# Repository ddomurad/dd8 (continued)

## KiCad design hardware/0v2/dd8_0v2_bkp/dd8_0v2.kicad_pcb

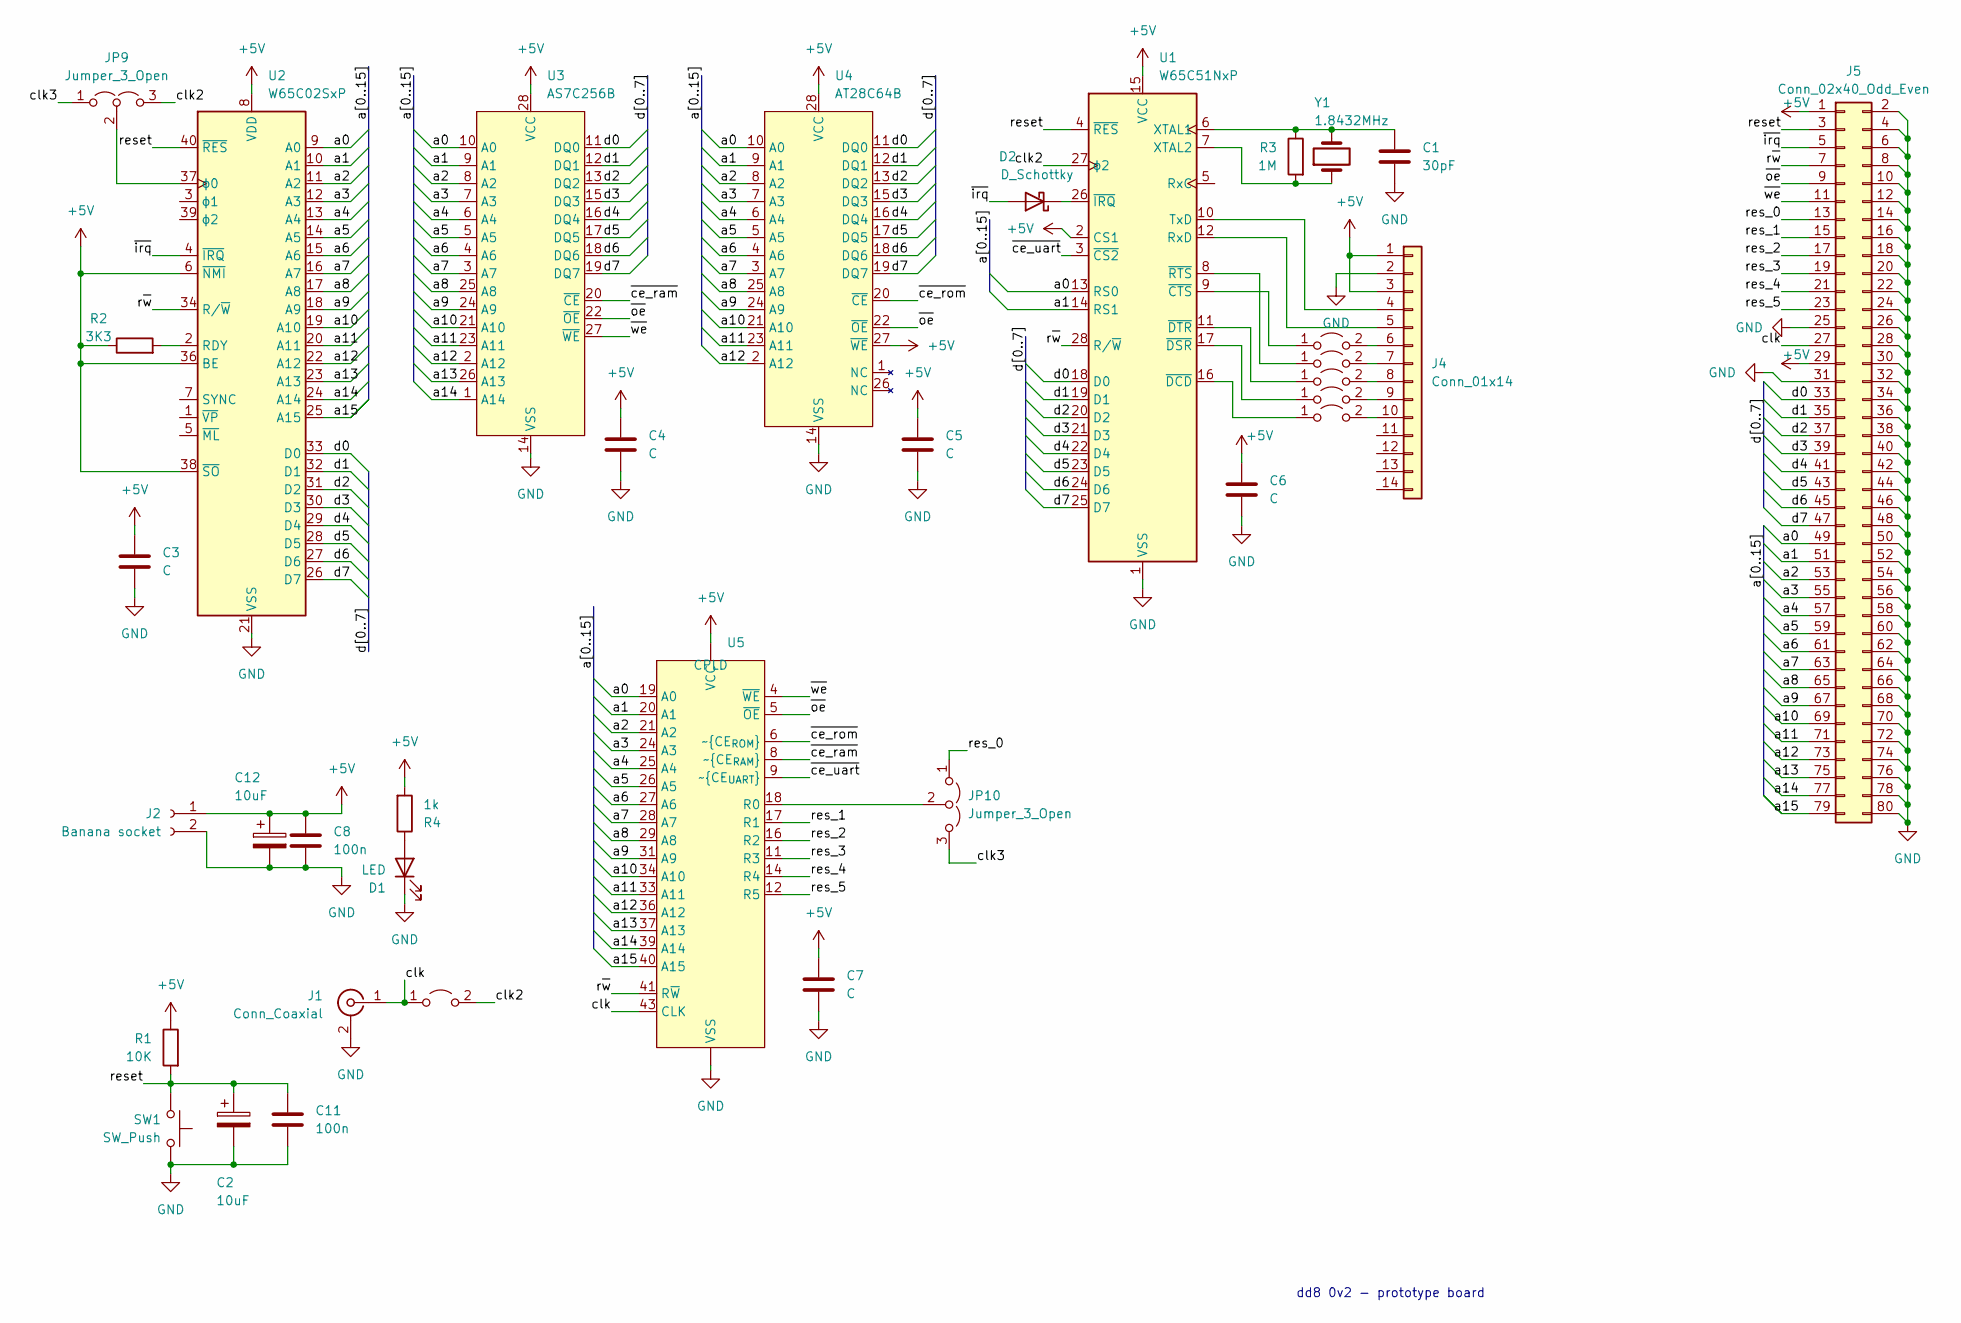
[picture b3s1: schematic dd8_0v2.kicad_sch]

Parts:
C1: 30pF; C_Disc_D3.0mm_W1.6mm_P2.50mm
C2, C12: 10uF; CP_Radial_D5.0mm_P2.50mm
C3, C4, C5, C6, C7: C; C_Disc_D3.0mm_W1.6mm_P2.50mm
C8, C11: 100n; C_Disc_D3.0mm_W1.6mm_P2.50mm
D1: LED; LED_D3.0mm
D2: D_Schottky; D_A-405_P7.62mm_Horizontal
J1: Conn_Coaxial; BNC_Amphenol_B6252HB-NPP3G-50_Horizontal
J2: Banana socket; Bannana_Jack_2Pin
J4: Conn_01x14; PinHeader_2x07_P2.54mm_Vertical
J5: Conn_02x40_Odd_Even; PinSocket_2x40_P2.54mm_Vertical
JP1, JP2, JP3, JP4, JP5, JP6: Jumper_2_Open; SolderJumper-2_P1.3mm_Open_Pad1.0x1.5mm
JP9, JP10: Jumper_3_Open; SolderJumper-3_P1.3mm_Open_Pad1.0x1.5mm
R1: 10K; R_Axial_DIN0204_L3.6mm_D1.6mm_P2.54mm_Vertical
R2: 3K3; R_Axial_DIN0204_L3.6mm_D1.6mm_P2.54mm_Vertical
R3: 1M; R_Axial_DIN0204_L3.6mm_D1.6mm_P5.08mm_Horizontal
R4: 1k; R_Axial_DIN0204_L3.6mm_D1.6mm_P2.54mm_Vertical
SW1: SW_Push; SW_PUSH_6mm_H5mm
U1: W65C51NxP; DIP-28_W15.24mm
U2: W65C02SxP; DIP-40_W15.24mm
U3: AS7C256B; DIP-28_W7.62mm
U4: AT28C64B; DIP_Socket-28_W6.9_W7.62_W10.16_W12.7_W13.5_3M_228-4817-00-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
U5: CPLD; PLCC-44_THT-Socket
Y1: 1.8432MHz; Crystal_HC18-U_Vertical

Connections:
+5V: C3.1, C4.1, C5.1, C6.1, C7.1, C8.1, C12.1, J2.1, J4.1, J4.3, J5.1, J5.29, R1.1, R2.1, R4.2, U1.2 (CS1), U1.15 (VCC), U2.6 (~NMI), U2.8 (VDD), U2.36 (BE), U2.38 (~SO), U3.28 (VCC), U4.27 (~WE), U4.28 (VCC), U5. (VCC)
/a0: J5.49, U1.13 (RS0), U2.9 (A0), U3.10 (A0), U4.10 (A0), U5.19 (A0)
/a1: J5.51, U1.14 (RS1), U2.10 (A1), U3.9 (A1), U4.9 (A1), U5.20 (A1)
/a2: J5.53, U2.11 (A2), U3.8 (A2), U4.8 (A2), U5.21 (A2)
/a3: J5.55, U2.12 (A3), U3.7 (A3), U4.7 (A3), U5.24 (A3)
/a4: J5.57, U2.13 (A4), U3.6 (A4), U4.6 (A4), U5.25 (A4)
/a5: J5.59, U2.14 (A5), U3.5 (A5), U4.5 (A5), U5.26 (A5)
/a6: J5.61, U2.15 (A6), U3.4 (A6), U4.4 (A6), U5.27 (A6)
/a7: J5.63, U2.16 (A7), U3.3 (A7), U4.3 (A7), U5.28 (A7)
/a8: J5.65, U2.17 (A8), U3.25 (A8), U4.25 (A8), U5.29 (A8)
/a9: J5.67, U2.18 (A9), U3.24 (A9), U4.24 (A9), U5.31 (A9)
/a10: J5.69, U2.19 (A10), U3.21 (A10), U4.21 (A10), U5.34 (A10)
/a11: J5.71, U2.20 (A11), U3.23 (A11), U4.23 (A11), U5.33 (A11)
/a12: J5.73, U2.22 (A12), U3.2 (A12), U4.2 (A12), U5.36 (A12)
/a13: J5.75, U2.23 (A13), U3.26 (A13), U5.37 (A13)
/a14: J5.77, U2.24 (A14), U3.1 (A14), U5.39 (A14)
/a15: J5.79, U2.25 (A15), U5.40 (A15)
/clk: J1.1 (In), J5.27, JP6.1 (A), U5.43 (CLK)
/clk2: JP6.2 (B), JP9.3 (B), U1.27 (ϕ2)
/clk3: JP9.1 (A), JP10.3 (B)
/d0: J5.33, U1.18 (D0), U2.33 (D0), U3.11 (DQ0), U4.11 (DQ0)
/d1: J5.35, U1.19 (D1), U2.32 (D1), U3.12 (DQ1), U4.12 (DQ1)
/d2: J5.37, U1.20 (D2), U2.31 (D2), U3.13 (DQ2), U4.13 (DQ2)
/d3: J5.39, U1.21 (D3), U2.30 (D3), U3.15 (DQ3), U4.15 (DQ3)
/d4: J5.41, U1.22 (D4), U2.29 (D4), U3.16 (DQ4), U4.16 (DQ4)
/d5: J5.43, U1.23 (D5), U2.28 (D5), U3.17 (DQ5), U4.17 (DQ5)
/d6: J5.45, U1.24 (D6), U2.27 (D6), U3.18 (DQ6), U4.18 (DQ6)
/d7: J5.47, U1.25 (D7), U2.26 (D7), U3.19 (DQ7), U4.19 (DQ7)
/res_0: J5.13, JP10.1 (A)
/res_1: J5.15, U5.17 (R1)
/res_2: J5.17, U5.16 (R2)
/res_3: J5.19, U5.11 (R3)
/res_4: J5.21, U5.14 (R4)
/res_5: J5.23, U5.12 (R5)
/reset: C2.1, C11.1, J5.3, R1.2, SW1.2, U1.4 (~RES), U2.40 (~RES)
/r~w: J5.7, U1.28 (R/~W), U2.34 (R/~W), U5.41 (R~W)
/~ce_ram: U3.20 (~CE), U5.8 (~CE_{RAM})
/~ce_rom: U4.20 (~CE), U5.6 (~CE_{ROM})
/~ce_uart: U1.3 (~CS2), U5.9 (~CE_{UART})
/~irq: D2.2 (A), J5.5, U2.4 (~IRQ)
/~oe: J5.9, U3.22 (~OE), U4.22 (~OE), U5.5 (~OE)
/~we: J5.11, U3.27 (~WE), U5.4 (~WE)
GND: C1.2, C2.2, C3.2, C4.2, C5.2, C6.2, C7.2, C8.2, C11.2, C12.2, D1.1 (K), J1.2 (Ext), J2.2, J4.2, J5.2, J5.4, J5.6, J5.8, J5.10, J5.12, J5.14, J5.16, J5.18, J5.20, J5.22, J5.24, J5.25, J5.26, J5.28, J5.30, J5.31, J5.32, J5.34, J5.36, J5.38, J5.40, J5.42, J5.44, J5.46, J5.48, J5.50, J5.52, J5.54, J5.56, J5.58, J5.60, J5.62, J5.64, J5.66, J5.68, J5.70, J5.72, J5.74, J5.76, J5.78, J5.80, SW1.1, U1.1 (VSS), U2.21 (VSS), U3.14 (VSS), U4.14 (VSS), U5. (VCC)
unnamed: D1.2 (A), R4.1
unnamed: D2.1 (K), U1.26 (~IRQ)
unnamed: J4.4, U1.10 (TxD)
unnamed: J4.5, U1.12 (RxD)
unnamed: J4.6, JP1.2 (B)
unnamed: J4.7, JP2.2 (B)
unnamed: J4.8, JP3.2 (B)
unnamed: J4.9, JP4.2 (B)
unnamed: J4.10, JP5.2 (B)
unnamed: JP1.1 (A), U1.9 (~CTS)
unnamed: JP2.1 (A), U1.8 (~RTS)
unnamed: JP3.1 (A), U1.11 (~DTR)
unnamed: JP4.1 (A), U1.17 (~DSR)
unnamed: JP5.1 (A), U1.16 (~DCD)
unnamed: JP9.2 (C), U2.37 (ϕ0)
unnamed: JP10.2 (C), U5.18 (R0)
unnamed: C1.1, R3.1, U1.6 (XTAL1), Y1.2
unnamed: R3.2, U1.7 (XTAL2), Y1.1
unnamed: R2.2, U2.2 (RDY)

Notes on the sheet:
dd8 0v2 - prototype board

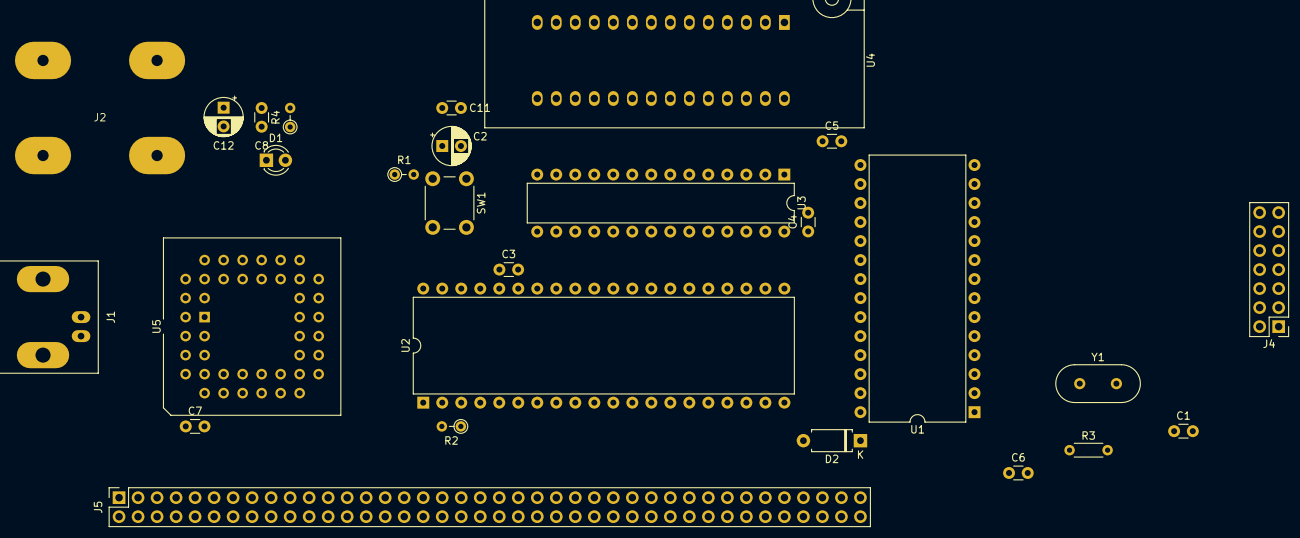
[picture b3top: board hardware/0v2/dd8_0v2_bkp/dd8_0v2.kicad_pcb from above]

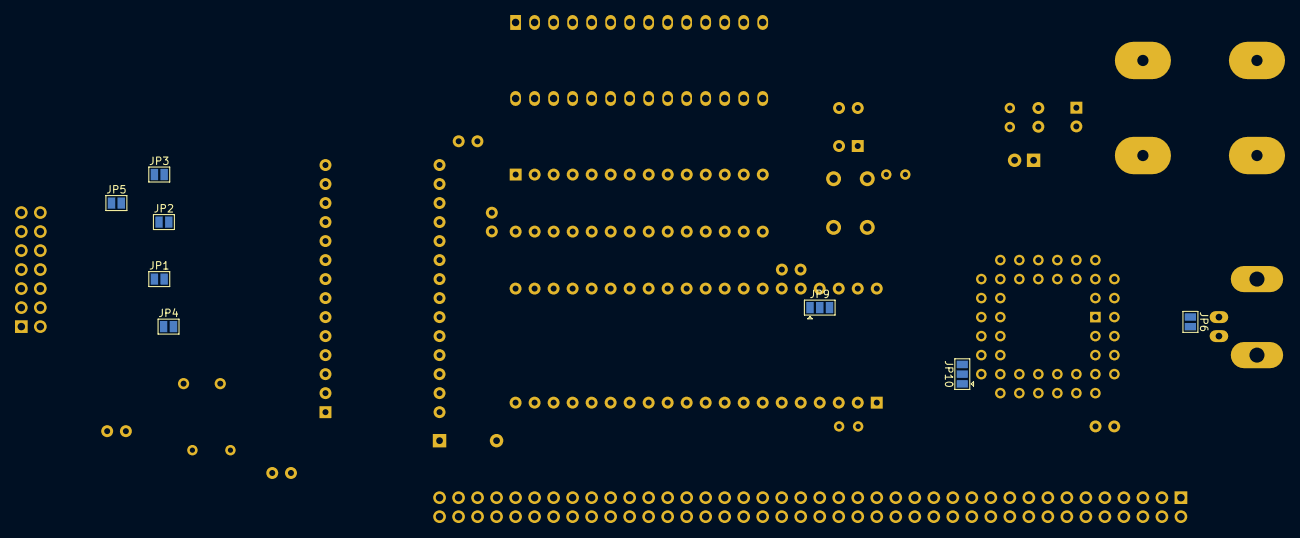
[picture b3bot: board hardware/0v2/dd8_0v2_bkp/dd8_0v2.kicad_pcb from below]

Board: 2 copper layers, 35 parts (8 on the bottom side), 62 nets.

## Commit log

2023-10-01 Arduino 6502 interface
2023-10-01 Run first test program
2023-10-03 Initial assembler implementations
2023-10-14 Refactor to antlr4
2023-10-14 basic preprocessor added
2023-10-14 naming refactored
2023-10-14 tests and updates
2023-10-15 basic error handling terminal compiler
2023-10-15 extend intr. set
2023-10-22 Assembler updates
2023-10-22 Cleanup & refactor
2023-10-23 Refactor and cleanup
2023-10-23 Updates, fixes and refactoring
2023-10-24 Add .db and .dw
2023-11-08 Add ram
2023-11-10 asm refactor
2023-11-24 cleanup
2023-12-10 dd8 v0.1 updated
2023-12-15 Arduino ROM emulator
2023-12-15 Spelling
2023-12-15 Refactoring
2023-12-16 Update dd8asm
2023-12-16 dd8asm cleanup
2023-12-17 asm updated
2023-12-17 Add math expressions
2023-12-17 expr updated
2023-12-18 before refactor
2023-12-25 Fix expression evaluation
2023-12-25 Refactor
2023-12-25 fix minu
2023-12-25 todo update
2023-12-25 update package name
2023-12-25 rename package
2023-12-26 update asm
2023-12-30 Add source listing
2024-01-06 Work on 0v2
2024-02-25 A lot of updates
2024-03-05 WIP Templates
2024-03-10 Implement templates
2024-03-10 test additional case
2024-03-10 add context based map
2024-03-10 add test with nested template labels
2024-03-10 fix nested templates listing
2024-03-17 update templates
2024-03-18 add test
2024-03-23 fix tests
2024-03-24 sim test
2024-03-25 note
2024-03-30 asm update
2024-04-20 work on w65c02 simulator
2024-04-26 sim update + experiments
2024-06-09 gfx poc
2024-11-05 Major graphics card update
